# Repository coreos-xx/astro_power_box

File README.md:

# Astro Power Box 

## Overview

PBV1 Power Distribution Box is designed for **astrophotography setups**, allowing users to efficiently power and control their astronomical equipment. It provides multiple **USB and 12V outputs**, making it an essential component for **observatory automation** and **field setups**.

## Key Features

✅ 4 switchable **USB 2.0 ports** (3A max per port)\
✅ 4 switchable **12V output ports** (3A max per port)\
✅ Configurable **persistent boot states** for outputs\
✅ **ASCOM and INDI driver** support for remote control\
✅ **Bluetooth connectivity** for serial communication\
✅ Supports up to **150W of total power distribution**

## Technical Specifications

### **Electrical**

| Specification       | Max | Typical | Min |
| ------------------- | --- | ------- | --- |
| Input Voltage (Vin) | 15V | 12V     | 5V  |
| Power Consumption   | 15A | -       | -   |
| USB2 Ports          | 4   | -       | -   |
| 12V Outputs         | 4   | -       | -   |

### **Physical**

| Specification | Value                       |
| ------------- | --------------------------- |
| Dimensions    | 110 mm x 100 mm x 31 mm     |
| Weight        | 250 grams                   |
| Enclosure     | Plastic (PLA thermoplastic) |
| Mounting      | Pre-drilled holes           |

### **Environmental Conditions**

| Condition             | Range                    |
| --------------------- | ------------------------ |
| Operating Temperature | -10°C to 50°C            |
| Storage Temperature   | -20°C to 60°C            |
| Humidity Range        | 10%-90% (non-condensing) |

## Directory Structure

```
astro_power_box/
├── cad/         # 3D enclosure design (STEP)
├── code/        # MCU firmware (Arduino)
├── doc/         # Documentation (LaTeX, images)
├── pcb/         # KiCad PCB design files
└── README.md    # Project overview
```

## Device Operation

The PBV1 allows individual control of **USB and 12V outputs** via **serial Bluetooth communication**. The outputs are managed through **dedicated ASCOM and INDI drivers**, enabling integration with astrophotography software like **KStars and N.I.N.A.**

### **Control Features**

- **Remote switch control** for USB and 12V outputs
- **Default power states** configurable via software
- **Real-time power monitoring** (if applicable)

## Setup Instructions

### **Windows Setup**

1. Connect the **12V XT30 connector** to PBV1.
2. Connect a **USB-A to USB-B cable** between the host computer and PBV1.
3. Ensure the computer is discoverable for **Bluetooth devices**.
4. In Windows **Bluetooth settings**, add a new device.
5. Select **HC-05** and enter **PIN: 1234**.
6. A new **Serial Port** will appear under **COM and LPT** in **Device Manager**.
7. Note the **Serial Port name (e.g., COM6)** for ASCOM driver setup in NINA.

### **ASCOM Driver Installation (Windows)**

1. Download the latest ASCOM driver: [Download Here](https://drive.google.com/drive/folders/1Y-2tLgOCcrt2SNI-Vw1phUzMPFCBjFHW?usp=drive_link)
2. Run the installer and follow on-screen instructions.
3. Open your **astrophotography software** and configure the driver.
4. Set the **Serial Bluetooth port** as shown in **Device Manager**.
5. Assign labels for outputs (default: Switch 1 to 8).

### **INDI Driver Installation (Linux/Mac)**

🚧 **Not Released Yet**

## **Setting Up Custom Boot Configuration for Outputs**

1. Download the **BT Serial Android app**: [Google Play Store](https://play.google.com/store/apps/details?id=de.kai_morich.serial_bluetooth_terminal)
2. Pair your phone with **PBV1 Bluetooth module (HC-05)**.
3. Connect to **BT Serial Terminal** (Baud rate: **9600**).
4. Send `eX` where `X = 0-7` to set default boot states.
5. The device confirms changes and requires a reboot.
6. If modifying multiple outputs, send multiple commands before rebooting.

## Wiring & Pinout Diagrams

📌 See `doc/figures/ConnectionDiagram.png` for the full wiring diagram.

## Troubleshooting & FAQs

- **Device not detected?** → Check drivers and connections.
- **Power issues?** → Verify fuse settings and power source.
- **USB ports not working?** → Try a different USB cable.

## License

📜 This project is licensed under the **MIT License**.

## Contributing

Contributions are welcome! Open an **issue** or submit a **pull request**.

---

🚀 **PBV1 - Power Distribution Box for Astrophotography**

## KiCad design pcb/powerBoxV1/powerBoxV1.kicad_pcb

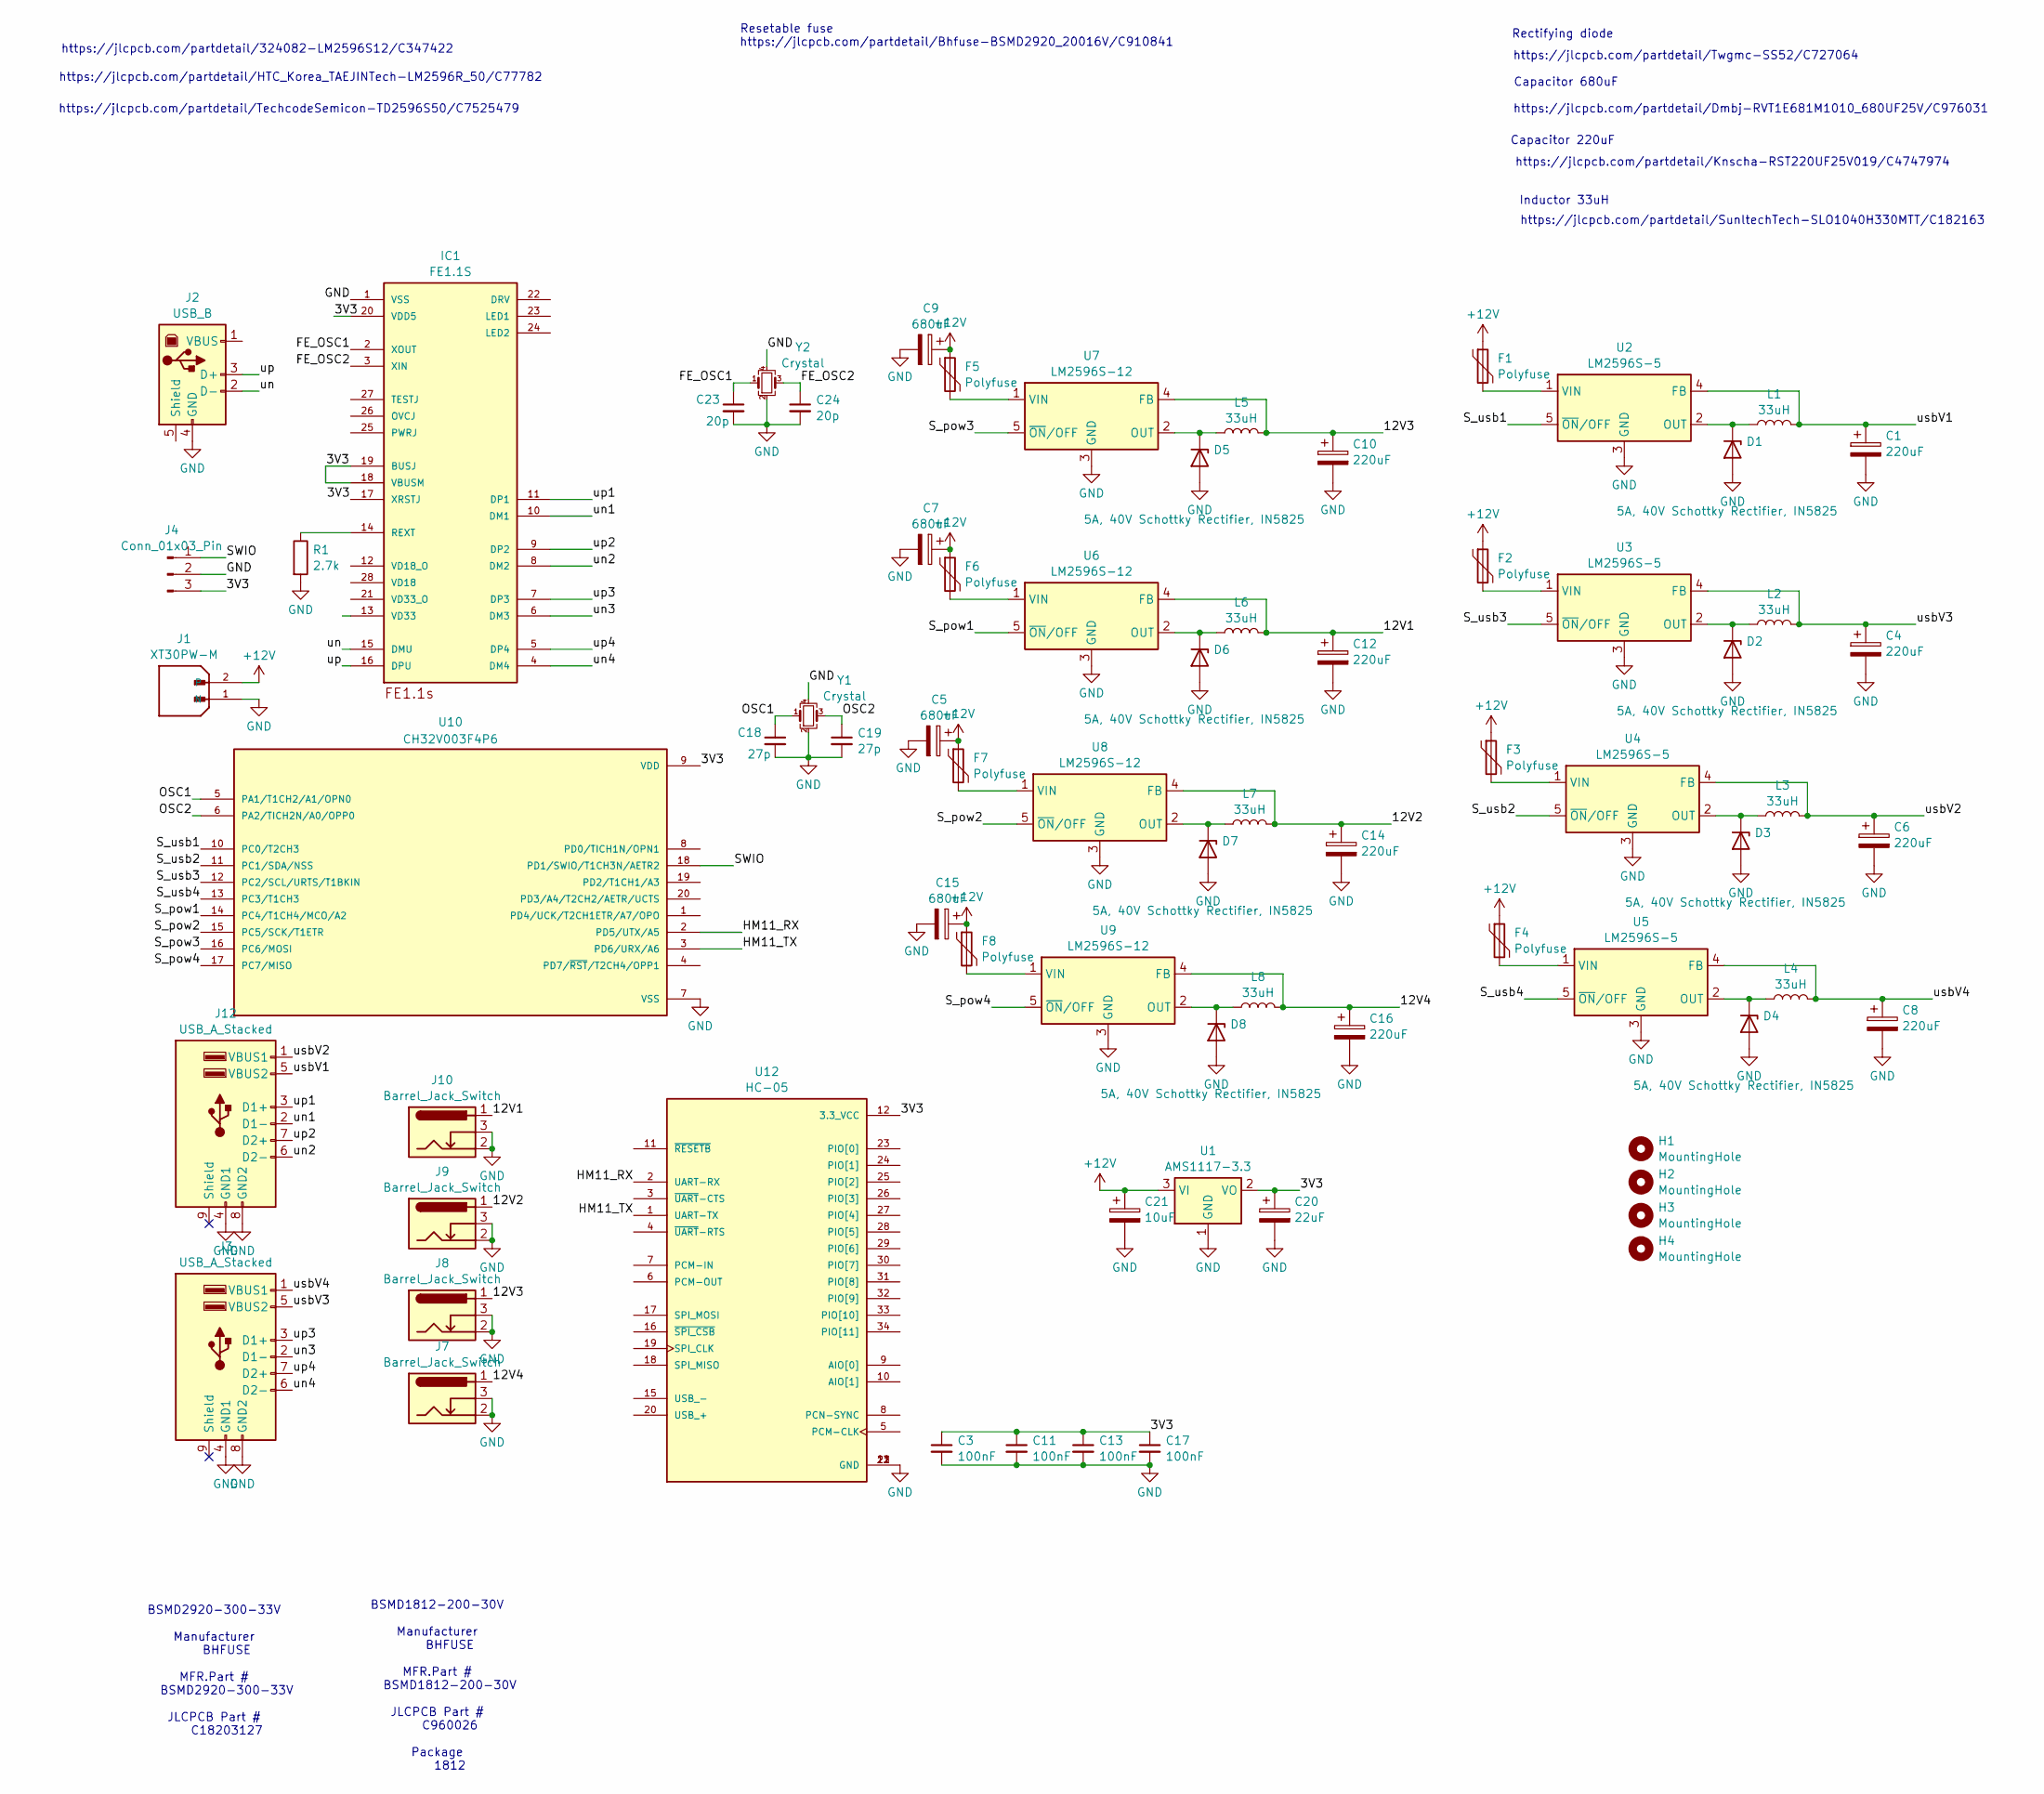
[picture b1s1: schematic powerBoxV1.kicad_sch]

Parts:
C1, C4, C6, C8, C10, C12, C14, C16: 220uF; CP_Elec_6.3x7.7
C3, C11, C13, C17: 100nF; C_0805_2012Metric
C5, C7, C9, C15: 680uF; CP_Elec_10x10.5
C18, C19: 27p; C_0805_2012Metric
C20: 22uF; CP_Elec_4x4.5
C21: 10uF; CP_Elec_4x4.5
C23, C24: 20p; C_0805_2012Metric
D1, D2, D3, D4, D5, D6, D7, D8: 5A, 40V Schottky Rectifier, IN5825; D_SMA
F1, F2, F3, F4: Polyfuse; Fuse_1812_4532Metric
F5, F6, F7, F8: Polyfuse; Fuse_2920_7451Metric
H1, H2, H3, H4: MountingHole; MountingHole_3.2mm_M3
IC1: FE1.1S; FE1.1S_SSOP-28
J1: XT30PW-M; AMASS_XT30PW-M_1x02_P2.50mm_Horizontal; PARTREV 1.2
J2: USB_B; USB_B_OST_USB-B1HSxx_Horizontal
J3, J12: USB_A_Stacked; USB_A_CUI_UJ2-ADH-TH_Horizontal_Stacked
J4: Conn_01x03_Pin; PinHeader_1x03_P2.54mm_Vertical
J7, J8, J9, J10: Barrel_Jack_Switch; BarrelJack_Horizontal
L1, L2, L3, L4, L5, L6, L7, L8: 33uH; L_10.4x10.4_H4.8
R1: 2.7k; R_0805_2012Metric
U1: AMS1117-3.3; SOT-223-3_TabPin2
U2, U3, U4, U5: LM2596S-5; TO-263-5_TabPin3
U6, U7, U8, U9: LM2596S-12; TO-263-5_TabPin3
U10: CH32V003F4P6; SOP65P640X121-20N; PARTREV 1.4
U12: HC-05; XCVR_HC-05; PARTREV v1.0
Y1, Y2: Crystal; Crystal_SMD_2520-4Pin_2.5x2.0mm

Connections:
+12V: C5.1, C7.1, C9.1, C15.1, C21.1, F1.1, F2.1, F3.1, F4.1, F5.1, F6.1, F7.1, F8.1, J1.2, U1.3 (VI)
/3V3: C3.1, C11.1, C13.1, C17.1, C20.1, IC1.17 (XRSTJ), IC1.18 (VBUSM), IC1.19 (BUSJ), IC1.20 (VDD5), J4.3, U1.2 (VO), U10.9 (VDD), U12.12 (3.3_VCC)
/12V1: C12.1, J10.1, L6.2, U6.4 (FB)
/12V2: C14.1, J9.1, L7.2, U8.4 (FB)
/12V3: C10.1, J8.1, L5.2, U7.4 (FB)
/12V4: C16.1, J7.1, L8.2, U9.4 (FB)
/FE_OSC1: C23.1, IC1.2 (XOUT), Y2.1
/FE_OSC2: C24.1, IC1.3 (XIN), Y2.3
/HM11_RX: U10.2 (PD5/UTX/A5), U12.2 (UART-RX)
/HM11_TX: U10.3 (PD6/URX/A6), U12.1 (UART-TX)
/OSC1: C18.1, U10.5 (PA1/T1CH2/A1/OPN0), Y1.1
/OSC2: C19.1, U10.6 (PA2/TICH2N/A0/OPP0), Y1.3
/SWIO: J4.1, U10.18 (PD1/SWIO/T1CH3N/AETR2)
/S_pow1: U6.5 (~ON/OFF), U10.14 (PC4/T1CH4/MCO/A2)
/S_pow2: U8.5 (~ON/OFF), U10.15 (PC5/SCK/T1ETR)
/S_pow3: U7.5 (~ON/OFF), U10.16 (PC6/MOSI)
/S_pow4: U9.5 (~ON/OFF), U10.17 (PC7/MISO)
/S_usb1: U2.5 (~ON/OFF), U10.10 (PC0/T2CH3)
/S_usb2: U4.5 (~ON/OFF), U10.11 (PC1/SDA/NSS)
/S_usb3: U3.5 (~ON/OFF), U10.12 (PC2/SCL/URTS/T1BKIN)
/S_usb4: U5.5 (~ON/OFF), U10.13 (PC3/T1CH3)
/un: IC1.15 (DMU), J2.2 (D-)
/un1: IC1.10 (DM1), J12.2 (D1-)
/un2: IC1.8 (DM2), J12.6 (D2-)
/un3: IC1.6 (DM3), J3.2 (D1-)
/un4: IC1.4 (DM4), J3.6 (D2-)
/up: IC1.16 (DPU), J2.3 (D+)
/up1: IC1.11 (DP1), J12.3 (D1+)
/up2: IC1.9 (DP2), J12.7 (D2+)
/up3: IC1.7 (DP3), J3.3 (D1+)
/up4: IC1.5 (DP4), J3.7 (D2+)
/usbV1: C1.1, J12.5 (VBUS2), L1.2, U2.4 (FB)
/usbV2: C6.1, J12.1 (VBUS1), L3.2, U4.4 (FB)
/usbV3: C4.1, J3.5 (VBUS2), L2.2, U3.4 (FB)
/usbV4: C8.1, J3.1 (VBUS1), L4.2, U5.4 (FB)
GND: C1.2, C3.2, C4.2, C5.2, C6.2, C7.2, C8.2, C9.2, C10.2, C11.2, C12.2, C13.2, C14.2, C15.2, C16.2, C17.2, C18.2, C19.2, C20.2, C21.2, C23.2, C24.2, D1.2 (A), D2.2 (A), D3.2 (A), D4.2 (A), D5.2 (A), D6.2 (A), D7.2 (A), D8.2 (A), IC1.1 (VSS), J1.1 (N), J2.4 (GND), J3.4 (GND1), J3.8 (GND2), J4.2, J7.2, J7.3, J8.2, J8.3, J9.2, J9.3, J10.2, J10.3, J12.4 (GND1), J12.8 (GND2), R1.2, U1.1 (GND), U2.3 (GND), U3.3 (GND), U4.3 (GND), U5.3 (GND), U6.3 (GND), U7.3 (GND), U8.3 (GND), U9.3 (GND), U10.7 (VSS), U12.13 (GND), U12.21 (GND), U12.22 (GND), Y1.2, Y1.4, Y2.2, Y2.4
unnamed: D1.1 (K), L1.1, U2.2 (OUT)
unnamed: D2.1 (K), L2.1, U3.2 (OUT)
unnamed: D3.1 (K), L3.1, U4.2 (OUT)
unnamed: D4.1 (K), L4.1, U5.2 (OUT)
unnamed: D5.1 (K), L5.1, U7.2 (OUT)
unnamed: D6.1 (K), L6.1, U6.2 (OUT)
unnamed: D7.1 (K), L7.1, U8.2 (OUT)
unnamed: D8.1 (K), L8.1, U9.2 (OUT)
unnamed: IC1.14 (REXT), R1.1
unnamed: F1.2, U2.1 (VIN)
unnamed: F2.2, U3.1 (VIN)
unnamed: F3.2, U4.1 (VIN)
unnamed: F4.2, U5.1 (VIN)
unnamed: F6.2, U6.1 (VIN)
unnamed: F5.2, U7.1 (VIN)
unnamed: F7.2, U8.1 (VIN)
unnamed: F8.2, U9.1 (VIN)

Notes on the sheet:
Inductor 33uH
https://jlcpcb.com/partdetail/Knscha-RST220UF25V019/C4747974
https://jlcpcb.com/partdetail/Bhfuse-BSMD2920_20016V/C910841
https://jlcpcb.com/partdetail/SunltechTech-SLO1040H330MTT/C182163
Capacitor 680uF
BSMD2920-300-33V Manufacturer BHFUSE MFR.Part # BSMD2920-300-33V JLCPCB Part # C18203127
BSMD1812-200-30V Manufacturer BHFUSE MFR.Part # BSMD1812-200-30V JLCPCB Part # C960026 Package 1812
https://jlcpcb.com/partdetail/Twgmc-SS52/C727064
https://jlcpcb.com/partdetail/324082-LM2596S12/C347422
https://jlcpcb.com/partdetail/HTC_Korea_TAEJINTech-LM2596R_50/C77782
https://jlcpcb.com/partdetail/Dmbj-RVT1E681M1010_680UF25V/C976031
Rectifying diode
https://jlcpcb.com/partdetail/TechcodeSemicon-TD2596S50/C7525479
Capacitor 220uF
Resetable fuse

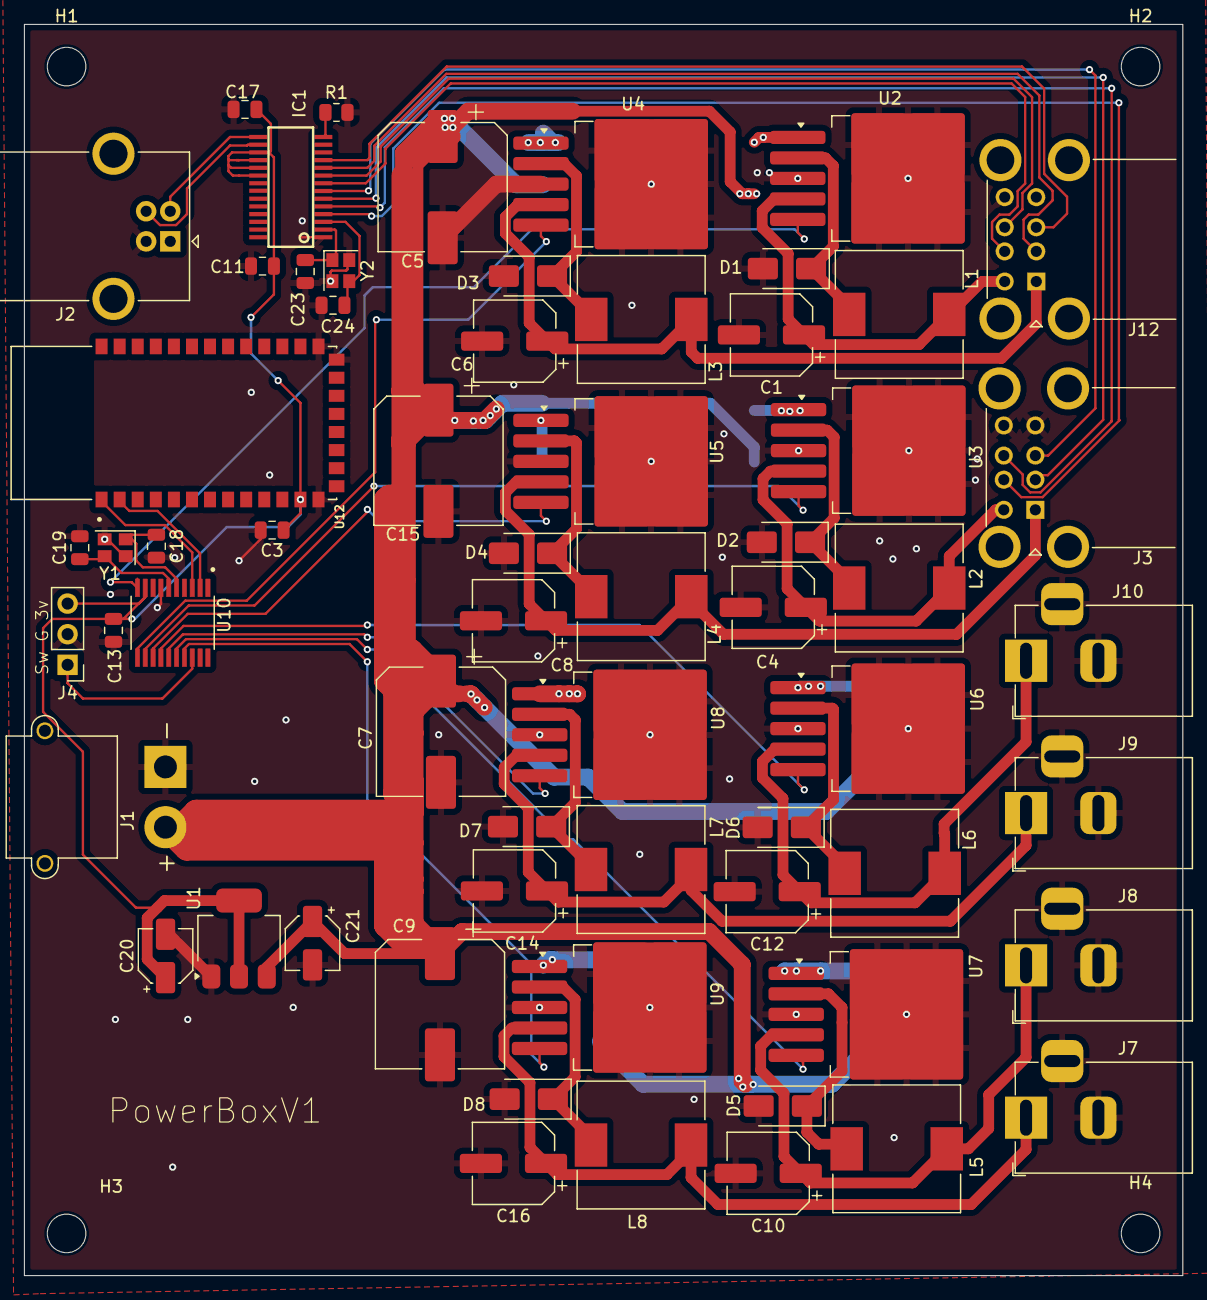
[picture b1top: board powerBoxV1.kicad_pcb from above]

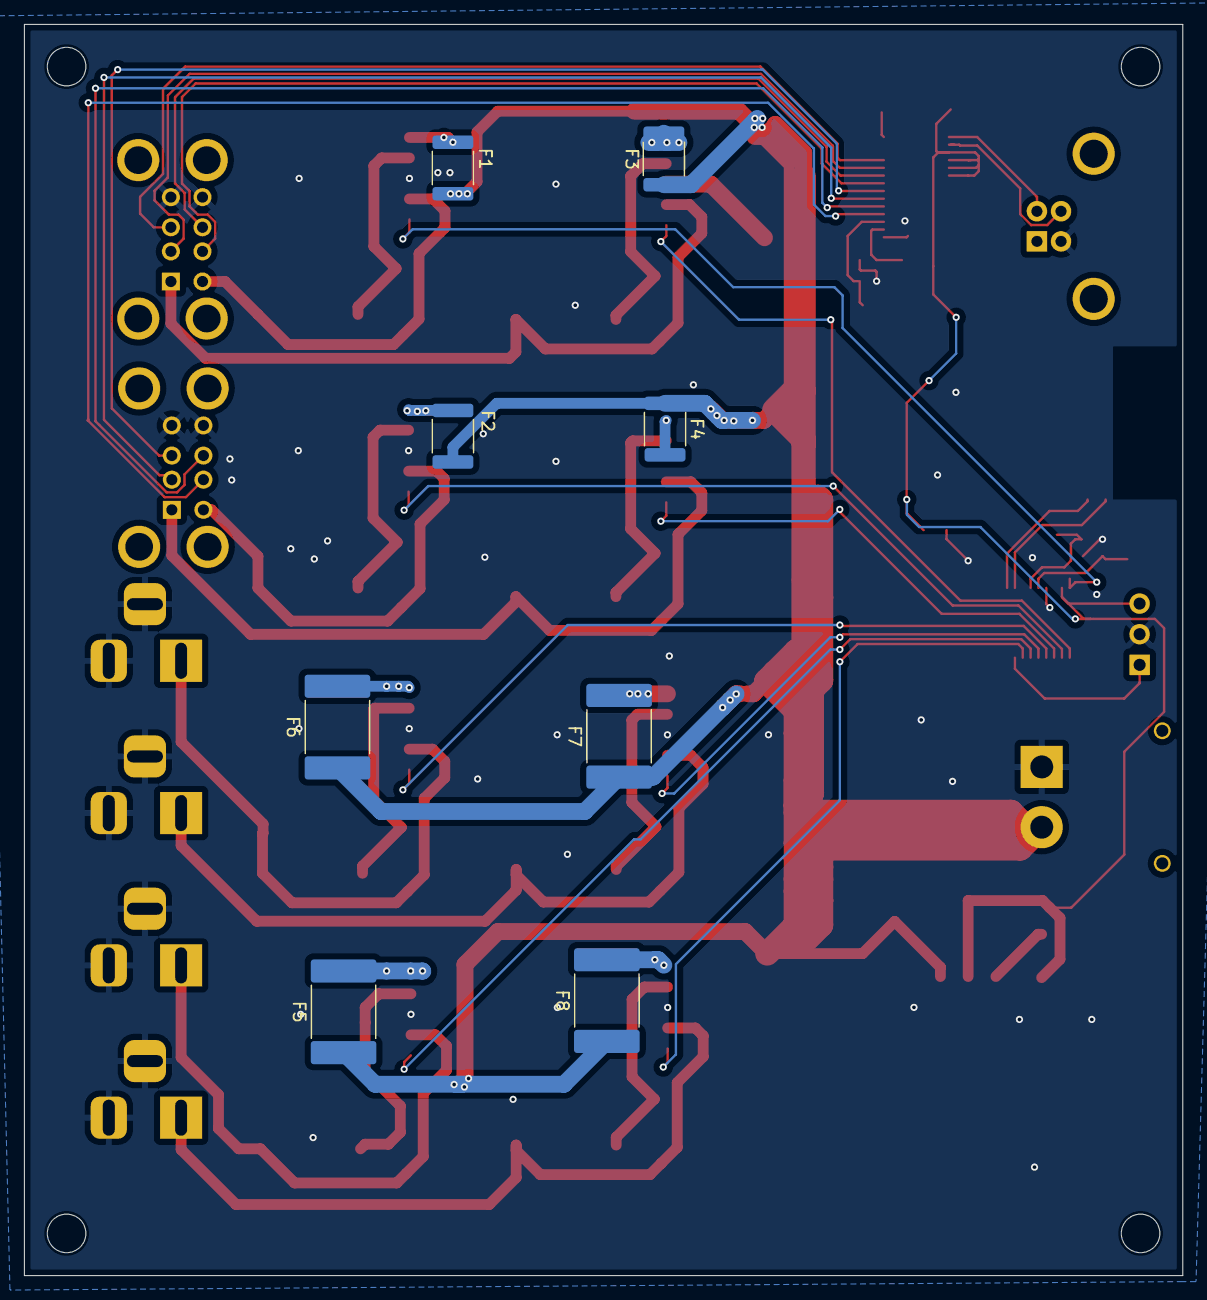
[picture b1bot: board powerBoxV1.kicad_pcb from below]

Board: 2 copper layers, 96.1 x 103.8 mm, 74 parts (8 on the bottom side), 53 nets.

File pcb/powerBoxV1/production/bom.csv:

Designator,Footprint,Quantity,Value,LCSC Part #
"C1, C10, C12, C14, C16, C4, C6, C8",CP_Elec_6.3x7.7,8,220uF,
"C11, C13, C17, C3",0805,4,100nF,
"C15, C5, C7, C9",CP_Elec_10x10.5,4,680uF,
"C18, C19",0805,2,27p,
C20,CP_Elec_4x4.5,1,22uF,
C21,CP_Elec_4x4.5,1,10uF,
"C23, C24",0805,2,20p,
"D1, D2, D3, D4, D5, D6, D7, D8",D_SMA,8,"5A, 40V Schottky Rectifier, IN5825",
"F1, F2, F3, F4",1812,4,Polyfuse,
"F5, F6, F7, F8",2920,4,Polyfuse,
IC1,FE1.1S_SSOP-28,1,FE1.1S,
J1,AMASS_XT30PW-M_1x02_P2.50mm_Horizontal,1,XT30PW-M,
"J10, J7, J8, J9",BarrelJack_Horizontal,4,Barrel_Jack_Switch,
"J12, J3",USB_A_CUI_UJ2-ADH-TH_Horizontal_Stacked,2,USB_A_Stacked,
J2,USB_B_OST_USB-B1HSxx_Horizontal,1,USB_B,
J4,PinHeader_1x03_P2.54mm_Vertical,1,Conn_01x03_Pin,
"L1, L2, L3, L4, L5, L6, L7, L8",L_10.4x10.4_H4.8,8,33uH,
R1,0805,1,2.7k,
U1,SOT-223-3_TabPin2,1,AMS1117-3.3,
U10,SOP65P640X121-20N,1,CH32V003F4P6,
U12,XCVR_HC-05,1,HC-05,
"U2, U3, U4, U5",TO-263-5_TabPin3,4,LM2596S-5,
"U6, U7, U8, U9",TO-263-5_TabPin3,4,LM2596S-12,
"Y1, Y2",Crystal_SMD_2520-4Pin_2.5x2.0mm,2,Crystal,

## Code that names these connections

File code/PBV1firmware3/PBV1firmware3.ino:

mmun#include <EEPROM.h>

#define OUT0 PC0
#define OUT1 PC1
#define OUT2 PC2
#define OUT3 PC3
#define OUT4 PC4
#define OUT5 PC5
#define OUT6 PC6
#define OUT7 PC7

#define EEPROM_MAGIC_BYTE 0x15  // A marker to check if EEPROM is initialized
#define EEPROM_ADDR_MAGIC 0      // EEPROM Address for magic byte
#define EEPROM_ADDR_STATES 1      // EEPROM Address where pin states start

int outArray[8] = {OUT0, OUT1, OUT2, OUT3, OUT4, OUT5, OUT6, OUT7};
boolean stateArray[8] = { LOW, LOW, LOW, LOW, LOW, LOW, LOW, LOW}; // Default states

void loadStateFromEEPROM() {
    EEPROM.begin(); // Initialize EEPROM

    byte magicByte = EEPROM.read(EEPROM_ADDR_MAGIC);
    if (magicByte == EEPROM_MAGIC_BYTE) {
        //Serial.println("Loading stored configuration...");
        for (int i = 0; i < 8; i++) {
            stateArray[i] = EEPROM.read(EEPROM_ADDR_STATES + i);
        }
    } else {
        //Serial.println("No valid config found. Using defaults.");
        saveStateToEEPROM();  // Save default states to EEPROM
    }
}

void saveStateToEEPROM() {
    EEPROM.begin();

    Serial.println("Saving configuration to EEPROM...");

    EEPROM.write(EEPROM_ADDR_MAGIC, EEPROM_MAGIC_BYTE);  // Write magic byte
    for (int i = 0; i < 8; i++) {
        EEPROM.write(EEPROM_ADDR_STATES + i, stateArray[i]);
    }
    EEPROM.commit();  // Save changes

    Serial.println("Configuration saved. Reboot required.");
}

void setup() {
    Serial.begin(9600);
    delay(1000);

    //Serial.println("CH32V003 EEPROM Debug Start");

    loadStateFromEEPROM();  // Load saved configuration or use default

    for (int i = 0; i < 8; i++) {
        pinMode(outArray[i], OUTPUT);
        digitalWrite(outArray[i], stateArray[i]);  // Apply stored states
    }
}

void loop() {
    if (Serial.available()) {
        char in = Serial.read(); // Read the first command character

        if (in == 's') {
            Serial.println(" ");
            int val = Serial.read();
            val = val - 48; // Convert ASCII to integer
            if (val >= 0 && val < 8) {
                stateArray[val] = !stateArray[val]; // Toggle state
                digitalWrite(outArray[val], stateArray[val]); // Update hardware
                Serial.println(!stateArray[val]); // Send new state
            } else {
                Serial.print("Invalid switch index ");
                Serial.println(val);
            }
        } else if (in == 'g') {
            Serial.println(" ");
            int val = Serial.read();
            val = val - 48;
            if (val >= 0 && val < 8) {
                Serial.println(!stateArray[val]); // Send current state
            } else {
                Serial.print("Invalid switch index ");
                Serial.println(val);
            }
        } else if (in == 'e') {
            Serial.println(" ");
            int val = Serial.read();
            val = val - 48;
            if (val >= 0 && val < 8) {
                stateArray[val] = !stateArray[val]; // Toggle stored boot state
                saveStateToEEPROM();  // Save new boot state to EEPROM
                Serial.println("Boot state updated. Reboot required.");
            } else {
                Serial.print("Invalid switch index ");
                Serial.println(val);
            }
        } else {
            Serial.flush(); // Clear invalid input
        }
    }
}

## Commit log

2025-03-16 Fist commit. Clean version of the procet. Everything tested and working
2025-03-16 Added README to projec
2025-03-16 added EEPROM lib firmware project folder
